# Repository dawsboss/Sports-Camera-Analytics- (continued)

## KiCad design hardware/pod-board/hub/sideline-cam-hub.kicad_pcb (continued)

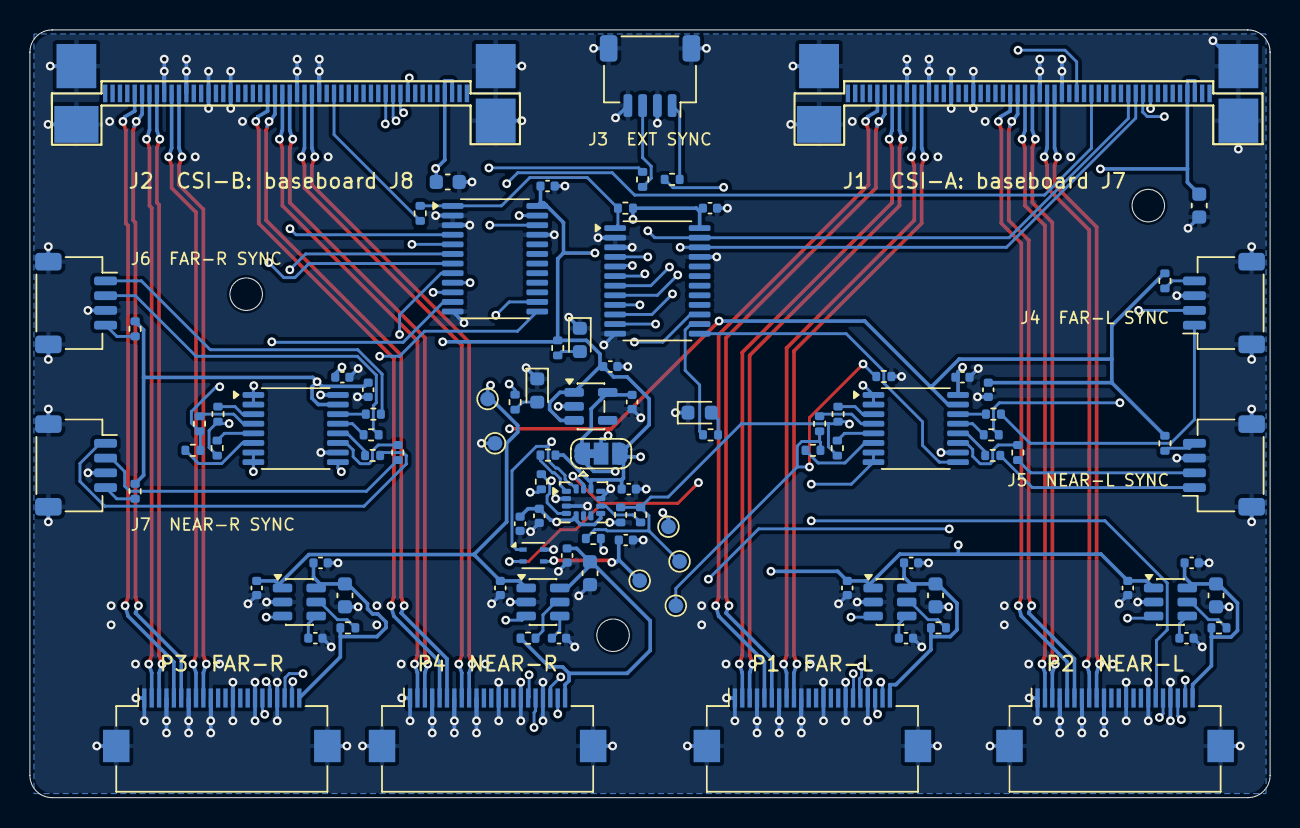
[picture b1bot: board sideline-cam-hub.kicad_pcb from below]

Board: 4 copper layers, 84.0 x 52.0 mm, 102 parts (102 on the bottom side), 111 nets.

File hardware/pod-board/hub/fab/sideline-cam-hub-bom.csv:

"Comment","Designator","Footprint","MPN","LCSC Part #","Quantity"
"1u","C10,C14,C18,C22,C30,C31,C51","Capacitor_SMD:C_0402_1005Metric","","","7"
"1n","C11,C15,C19,C23","Capacitor_SMD:C_0402_1005Metric","","","4"
"10u","C12,C16,C20,C24,C32,C33","Capacitor_SMD:C_0603_1608Metric","","","6"
"100n","C13,C17,C21,C25,C40-C45,C50,C52,C53","Capacitor_SMD:C_0402_1005Metric","","","13"
"green","D1-D3","LED_SMD:LED_0603_1608Metric","APT1608SGC","","3"
"WE 68715014522","J1,J2","sideline:WE_68715014522","68715014522","","2"
"SH 4-pin","J3-J7","Connector_JST:JST_SH_SM04B-SRSS-TB_1x04-1MP_P1.00mm_Horizontal","SM04B-SRSS-TB(LF)(SN)","","5"
"FH12-22S-0.5SH","P1-P4","Connector_FFC-FPC:Hirose_FH12-22S-0.5SH_1x22-1MP_P0.50mm_Horizontal","FH12-22S-0.5SH(55)","","4"
"2k2","R6","Resistor_SMD:R_0402_1005Metric","","","1"
"10k","R1,R7","Resistor_SMD:R_0402_1005Metric","","","2"
"47","R10,R12,R14,R16,R18,R20,R22,R24,R33,R34","Resistor_SMD:R_0402_1005Metric","","","10"
"33","R11,R13,R15,R17,R19,R21,R23,R25","Resistor_SMD:R_0402_1005Metric","","","8"
"0","R2,R3","Resistor_SMD:R_0402_1005Metric","","","2"
"100k","R30,R31","Resistor_SMD:R_0402_1005Metric","","","2"
"1k","R4,R5,R8,R32","Resistor_SMD:R_0402_1005Metric","","","4"
"100","R40-R43,R50-R53","Resistor_SMD:R_0402_1005Metric","","","8"
"AP2112K-1.8","U7","Package_TO_SOT_SMD:SOT-23-5","AP2112K-1.8TRG1","","1"
"ICM-42688-P","U10","Package_LGA:LGA-14_3x2.5mm_P0.5mm_LayoutBorder3x4y","ICM-42688-P","","1"
"SHT45-AD1B","U11","Sensor_Humidity:Sensirion_DFN-4_1.5x1.5mm_P0.8mm_SHT4x_NoCentralPad","SHT45-AD1B-R2","","1"
"PCA9555PW","U1,U2","Package_SO:TSSOP-24_4.4x7.8mm_P0.65mm","PCA9555PW,118","","2"
"TPS22917DBV","U3-U6","Package_TO_SOT_SMD:SOT-23-6","TPS22917DBVR","","4"
"SN74AVC4T774PW","U8,U9","Package_SO:TSSOP-16_4.4x5mm_P0.65mm","SN74AVC4T774PWR","","2"
